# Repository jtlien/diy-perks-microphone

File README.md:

# diy-perks-microphone
This is the Kicad implementation of a pc board for the DIY PERKS high performance microphone
Please become a subscriber to DIY PERKS channel on Youtube.
I have put this circuit into KICAD for those interested in putting it on a PC board.
I have not tested the board out yet.
The connection to the Volume control is a switch selecting one of 560 Ohm, 270 Ohm, 150 Ohm, 82 Ohm,
56 Ohm, 27 Ohm, 18 Ohm, 15 Ohm, 11 Ohm, 9.1 Ohm and 5.1 Ohm.
The microphone connection is to a 2N4416 Fet soldered directly to the outputs of the microphone cell.
The microphone capsule is a JLI2555.  I have included a .dxf file of the capsule case that has holes for the
sound.  It can be used to have the case made at an online laser cutting service.

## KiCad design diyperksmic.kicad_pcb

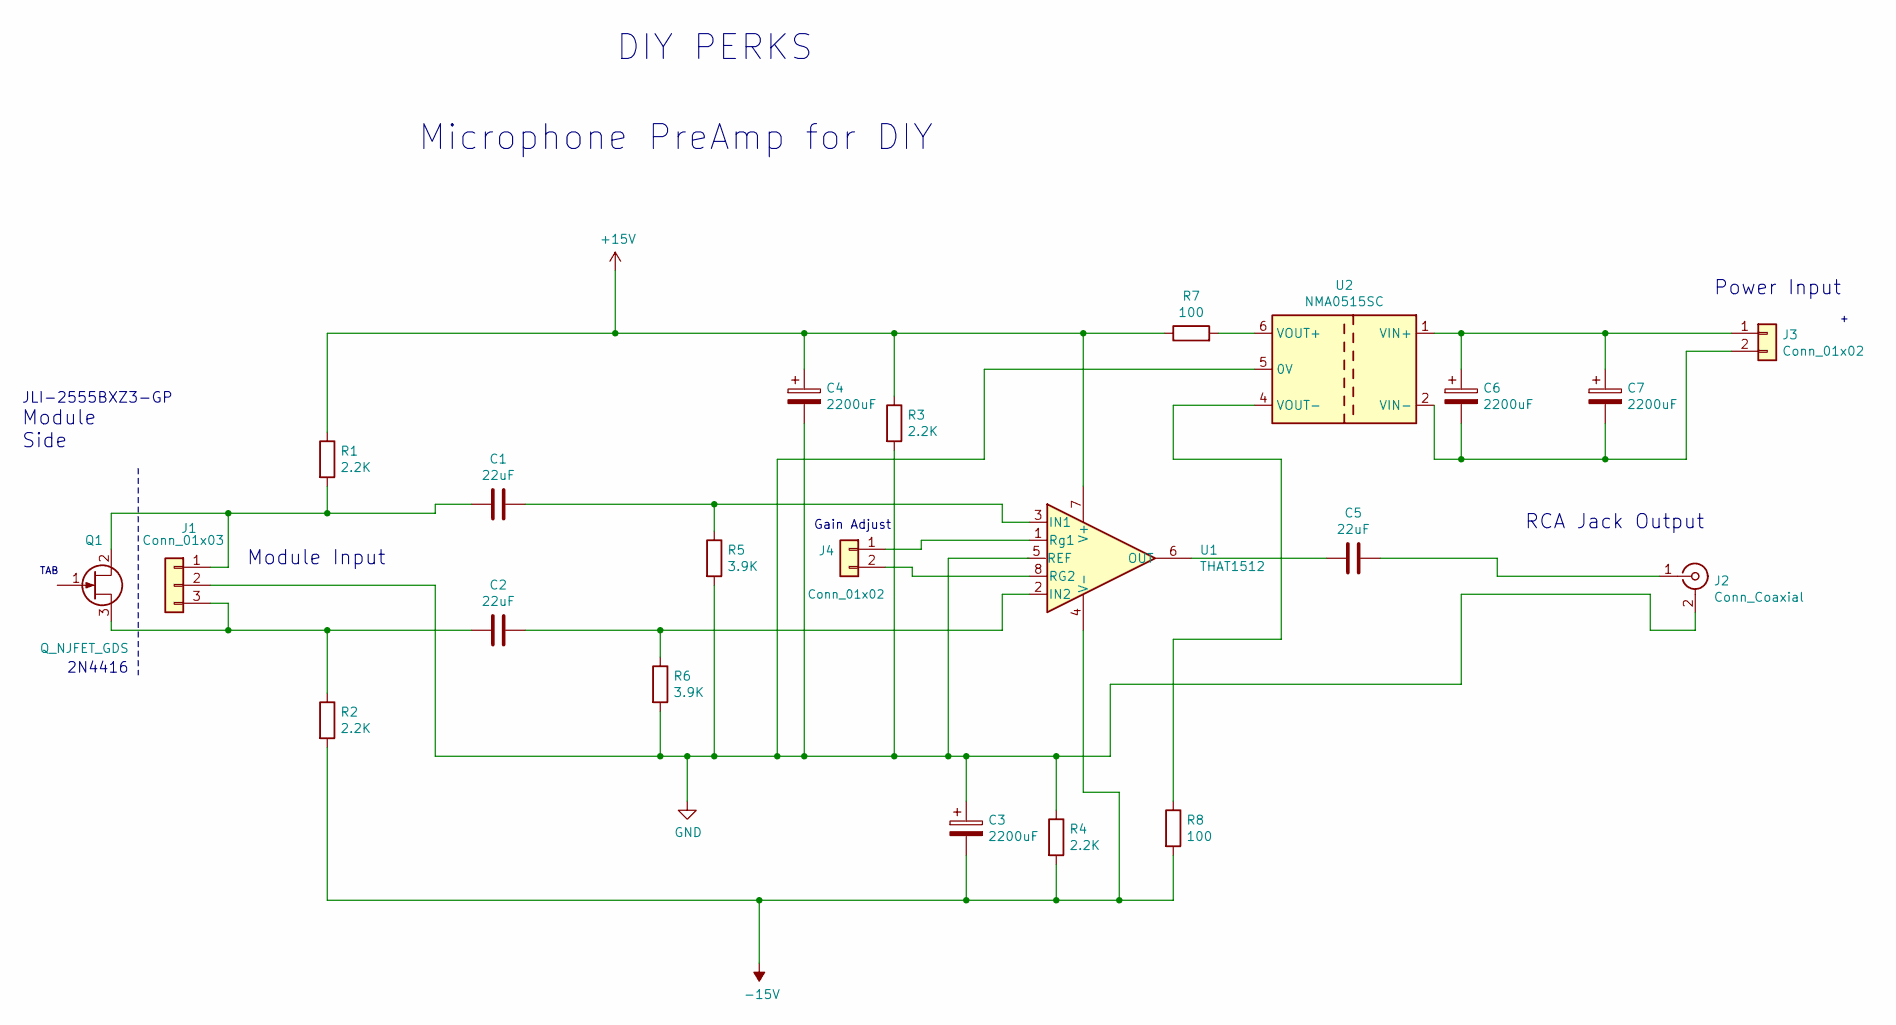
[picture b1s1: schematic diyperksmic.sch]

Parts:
C1, C2, C5: 22uF; C_Disc_D8.0mm_W5.0mm_P5.00mm
C3, C4, C6, C7: 2200uF; CP_Radial_D10.0mm_P3.80mm
J1: Conn_01x03; PinHeader_1x03_P2.54mm_Vertical
J2: Conn_Coaxial; CUI_RCJ-042
J3, J4: Conn_01x02; TerminalBlock_Phoenix_MKDS-1,5-2_1x02_P5.00mm_Horizontal
Q1: Q_NJFET_GDS
R1, R2, R3, R4: 2.2K; R_Axial_DIN0207_L6.3mm_D2.5mm_P10.16mm_Horizontal
R5, R6: 3.9K; R_Axial_DIN0207_L6.3mm_D2.5mm_P10.16mm_Horizontal
R7, R8: 100; R_Axial_DIN0207_L6.3mm_D2.5mm_P10.16mm_Horizontal
U1: THAT1512; DIP-8_W7.62mm
U2: NMA0515SC; Converter_DCDC_muRata_NMAxxxxSC_THT

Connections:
+15V: C4.1, R1.1, R3.1, R7.1, U1.7 (V+)
-15V: C3.2, R2.2, R4.2, R8.2, U1.4 (V-)
GND: C3.1, C4.2, J1.2, J2.2 (Ext), R3.2, R4.1, R5.2, R6.2, U2.5 (0V)
unnamed: C1.1, R5.1, U1.3 (IN1)
unnamed: C1.2, J1.1, Q1.2 (D), R1.2
unnamed: C2.1, R6.1, U1.2 (IN2)
unnamed: C2.2, J1.3, Q1.3 (S), R2.1
unnamed: C5.1, J2.1 (In)
unnamed: C5.2, U1.6 (OUT)
unnamed: C6.1, C7.1, J3.1, U2.1 (VIN+)
unnamed: C6.2, C7.2, J3.2, U2.2 (VIN-)
unnamed: J4.1, U1.1 (Rg1)
unnamed: J4.2, U1.8 (RG2)
unnamed: R7.2, U2.6 (VOUT+)
unnamed: R8.1, U2.4 (VOUT-)

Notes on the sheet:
Microphone PreAmp for DIY
2N4416
DIY PERKS
Gain Adjust
Power Input
RCA Jack Output
Module Input
Module Side
JLI-2555BXZ3-GP
TAB

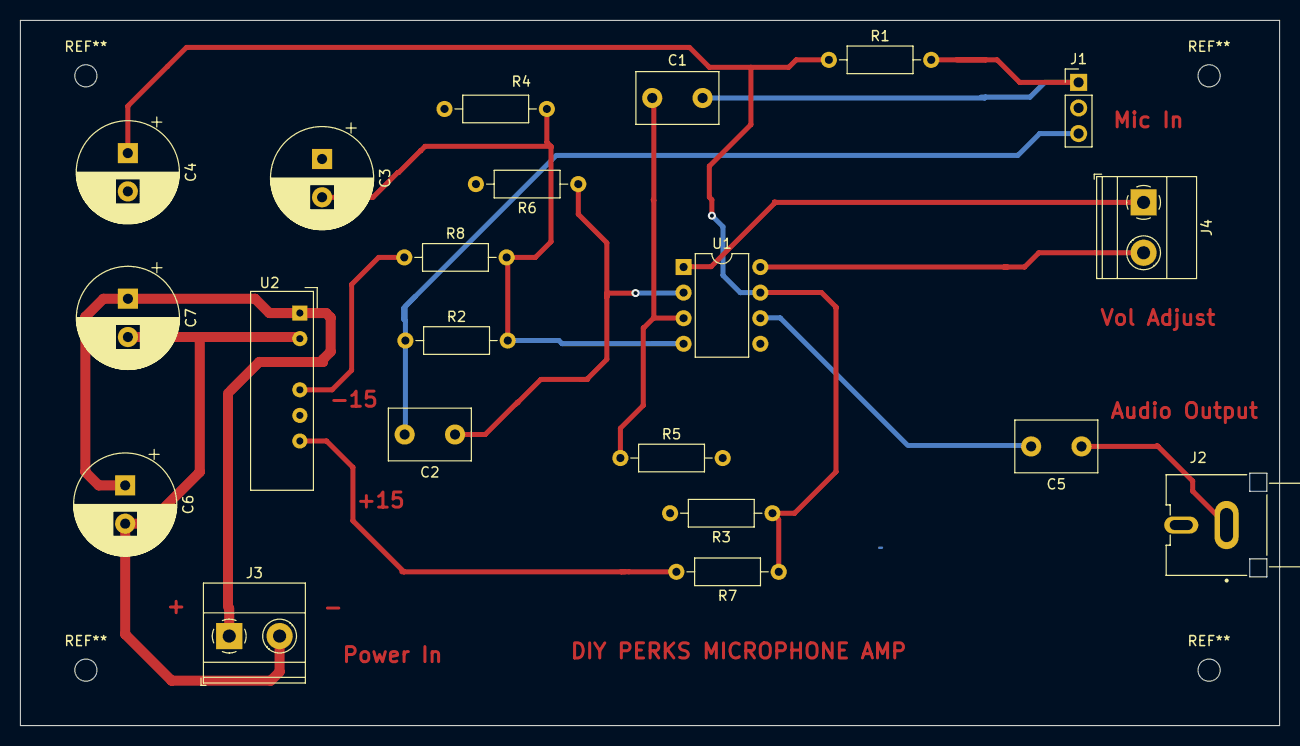
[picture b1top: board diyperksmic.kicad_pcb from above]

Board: 2 copper layers, 125.0 x 70.0 mm, 21 parts (0 on the bottom side), 15 nets.

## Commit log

2021-12-04 kicad files initial release
    First upload
2021-12-04 Addif info
2021-12-04 DXF file for microphone module added
2021-12-14 updated kicad board
    fix resistor sizes and cap sizes
2021-12-14 more board updates
    new .pro file
2021-12-14 updated gerbers to reflect pcb changes
    new release 12/13
